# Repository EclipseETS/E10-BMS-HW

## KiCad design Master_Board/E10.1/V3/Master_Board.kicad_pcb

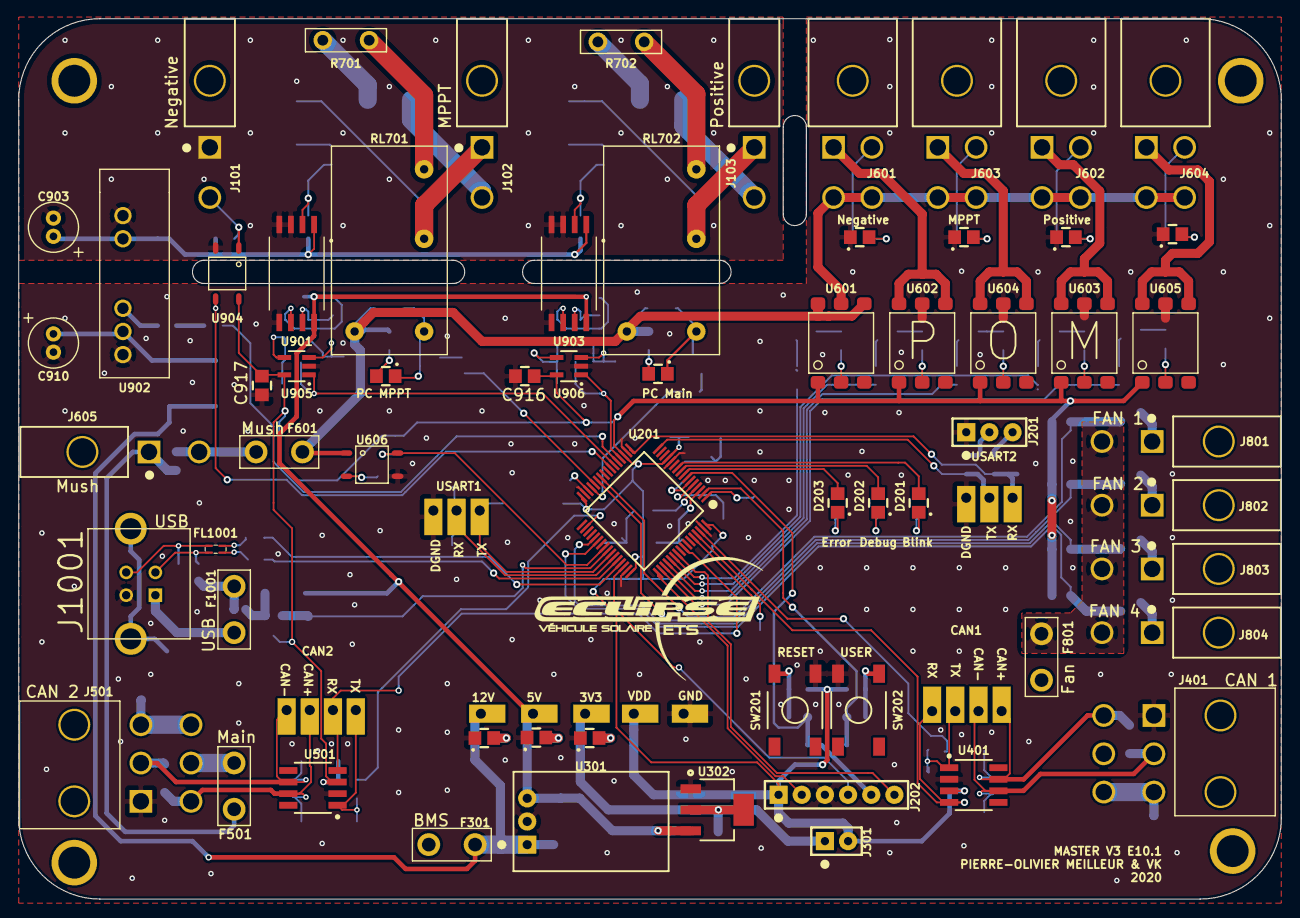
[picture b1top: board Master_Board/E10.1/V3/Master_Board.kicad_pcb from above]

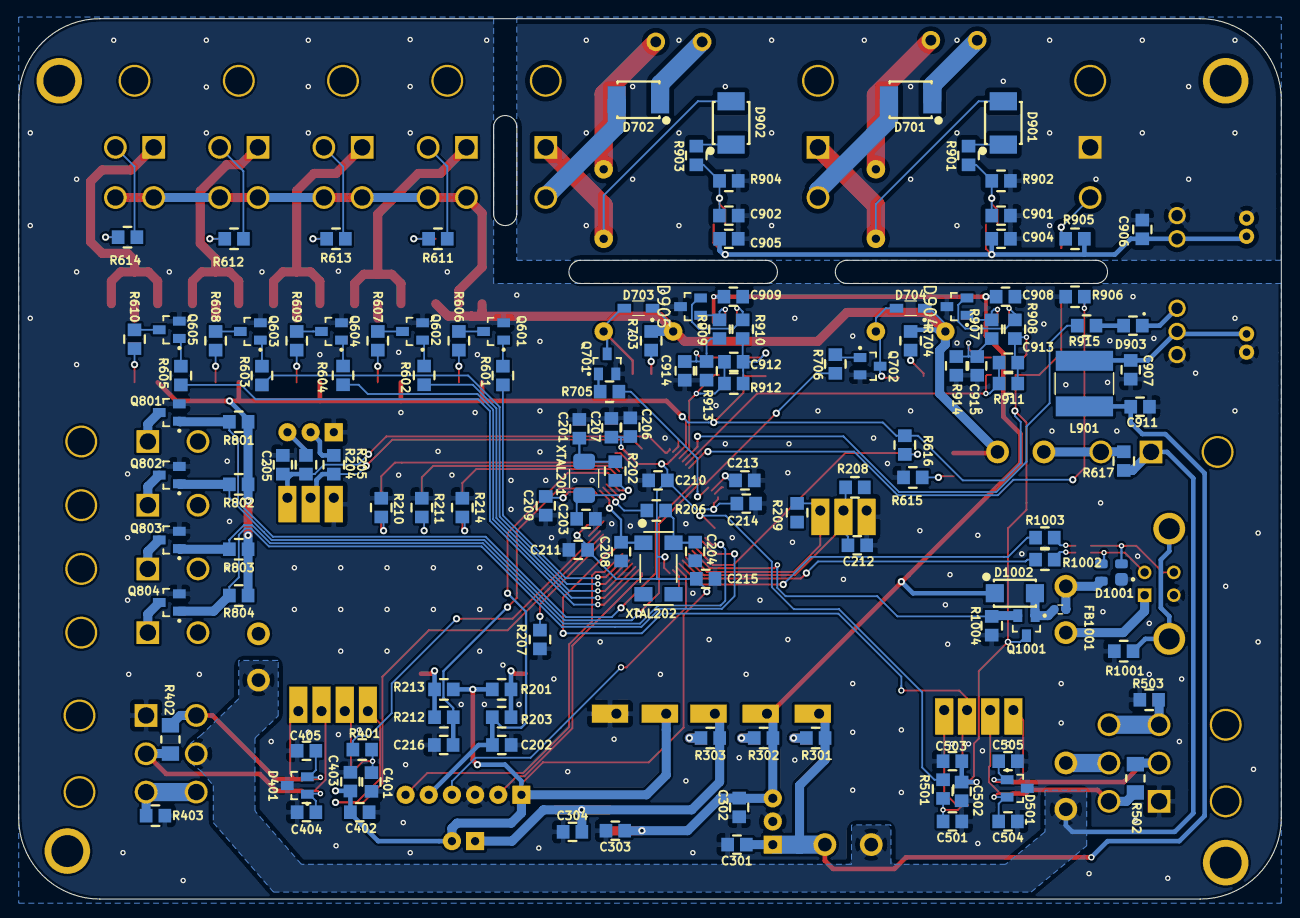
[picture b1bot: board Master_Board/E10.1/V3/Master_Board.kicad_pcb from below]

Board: 2 copper layers, 138.4 x 96.5 mm, 225 parts (139 on the bottom side), 145 nets.

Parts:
C201, C203, C205, C212, C404, C405, C504, C505: 885012007053; C0805
C202, C210, C211, C214, C215, C216, C403, C503, C904, C905, C906, C907, C908, C909, C916, C917: 885012207098; C0805
C204, C208: 885012007027; C0805
C206, C209, C402, C502: 885012107015; C0805
C207: 885012207092; C0805
C213, C301, C302: 885012107018; C0805
C303: 885012107014; C0805
C304: 885012107005; C0805
C401, C501, C901, C902, C912, C913, C914, C915: 885012207080; C0805
C903, C910: 860020472006; Radial-Can-5_11_2
C911: 885012207075; C0805
D201: 150080VS75000; LED_0805_GREEN
D202: 150080YS75000; LED_0805_YELLOW
D203: 150080RS75000; LED_0805_RED
D301, D302, D303, D601, D602, D603, D604, D705, D706: 150080BS75000; LED_0805_BLUE
D401, D501, D904, D905: D1213A-02SOL-7; SOT-23-3
D701, D702, D901, D902: NRVBS3200T3G; DO-214AA_SMB
D703, D704: NSR0530HT1G; SOD-323
D903: SD0805S020S1R0; Diode_0805
D1001: 8240026; SOT-143-4
D1002: B240AQ-13-F; DO-214AC_SMA
F301, F501, F601, F801: 39511000440; TE5_395
F1001: 39505000440; TE5_395
FB1001: 742792605; FB0603
FL1001: 744230900
H101, H102, H103, H104: Mounting-Hole-M3; Mounting_Hole_3mm
J101, J102, J103, J605, J801, J802, J803, J804: 649002227222
J201: Header_Male_Pin_2.54mm_1X3_,_Unshrouded; Headers_2.54mm_1X3
J202: Header_Male_Pin_2.54mm_1X6_,_Unshrouded; Headers_2.54mm_1X6
J301: Header_Male_Pin_2.54mm_1X2_,_Unshrouded; Headers_2.54mm_1X2
J401, J501: 649006227222
J601, J602, J603, J604: 649004227222
J1001: 61400413321
L901: 744052471; WE-TPC-SMD
Q601, Q602, Q603, Q604, Q605, Q701, Q702: BC849BLT1G; SOT-23-3
Q801, Q802, Q803, Q804, Q1001: BSS806NH6327XTSA1; SOT-23-3
R201, R204, R208, R213, R301, R905, R906, R1004: RC0805JR-074K7L; R0805
R202, R206, R403, R503, R1001, R1002, R1003: RC0805JR-070RL; R0805
R203, R212, R401, R501: RC0805JR-07100RL; R0805
R205, R209, R302, R611, R612, R613, R614, R703, R704: RC0805JR-071KL; R0805
R207, R601, R602, R603, R604, R605, R616, R705, R706, R801, R802, R803, R804, R902, R904, R907, R908, R909, R910: RC0805JR-0710KL; R0805
R210, R211, R214, R303, R915: RC0805JR-07470RL; R0805
R402, R502: RC1206JR-07120RL; R1206
R606, R607, R608, R609, R610: RC0805FR-071K1L; R0805
R615, R911, R912, R913, R914: RC0805JR-0715KL; R0805
R617: 0hms_0.5W; R0805
R701, R702: TR50JBC100R; TR50
R901, R903: RC0805JR-071ML; R0805
RL701, RL702: ALQ312
SW201, SW202: PTS645SM43SMTR92; PTS645_6X6X4_SMD
TP201, TP202, TP203, TP204, TP205, TP206, TP301, TP302, TP303, TP304, TP305, TP401, TP402, TP403, TP404, TP501, TP502, TP503, TP504: Test_Point_THM; Keystone_5001
U201: STM32F446RE; LQFP-64
U301: OKI-78SR-5_1.5-W36H-C; OKI-78SR_Horizontal
U302: AZ1117IH-3.3TRG1; SOT-223-3
U401, U501: SN65HVD232DR; SOIC-8
U601, U602, U603, U604, U605: TLP3543A(TP1,F; 6-SMD
U606, U904: CPC1117NTR; 4-SOP
U901, U903: ACPL-C87A-500E; SSO-8
U902: NCS1S2405SC
U905, U906: LMV321RILT; SOT-23-5
XTAL201: 7A-8.000MAHJ-T; TXC_7A_Series
XTAL202: ABS25-32.768KHZ-6-T; ABS25

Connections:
3.3V: C304.2, J301.1, R303.2, TP304.1, U302.2, U302.4
5V: C302.2, C303.2, C908.2, C909.2, D1002.1, R302.2, TP303.1, U301.3, U302.3, U901.8, U903.8
5V_HP: C903.1, C904.2, C905.2, C906.1, R905.1, U901.1, U902.6, U903.1
12V: C301.2, C911.1, F301.2, L901.2, R301.2, TP301.1, U301.1
/12V_Mush: D703.1, D704.1, F601.2, R703.1, R704.1, RL701.1, RL702.1, U601.4, U601.6, U606.1
/BOOT0: R207.2, U201.60
/CAN1/CAN_N: C404.1, D401.1, J401.2, R402.2, TP404.1, U401.6
/CAN1/CAN_P: C405.1, D401.2, J401.4, R402.1, TP403.1, U401.7
/CAN1/Shield1: J401.3, J401.6, R403.1
/CAN2/CAN2_H: C504.1, D501.2, J501.4, R502.1, TP503.1, U501.7
/CAN2/CAN2_L: C505.1, D501.1, J501.2, R502.2, TP504.1, U501.6
/CAN2/Shield2: J501.3, J501.6, R503.1
/Fan Control/12V_FANS: F801.2, J801.2, J802.2, J803.2, J804.2
/HV_High_Side+: D702.2, J103.2
/HV_High_Side-: D902.2, J103.1, RL702.3
/HV_Low_Side+: J101.2, R905.2, U904.1
/HV_Mppt+: D701.2, J102.2
/HV_Mppt-: D901.2, J102.1, RL701.3
/NRST: C202.1, J202.5, R203.2, U201.7
/PA4: C912.1, R912.2, U201.20, U906.1
/PA5: R915.2, U201.21
/PA6: C913.2, R911.2, U201.22, U905.1
/PA7: R906.1, U201.23, U904.3
/PA8: Q1001.2, R1004.1, U201.41
/PA11: R1002.2, U201.44
/PA12: R1003.2, U201.45
/PA15: R605.1, U201.50
/PB0: Q801.1, R801.2, U201.26
/PB1: Q802.1, R802.2, U201.27
/PB2: R706.2, U201.28
/PB5: TP502.1, U201.57, U501.4
/PB8: TP402.1, U201.61, U401.4
/PB9: R401.1, U201.62
/PB10: R705.2, U201.29
/PB13: R501.1, U201.34
/PC0: D203.2, U201.8
/PC1: D202.2, U201.9
/PC2: D201.2, U201.10
/PC6: Q803.1, R803.2, U201.37
/PC7: Q804.1, R804.2, U201.38
/PC9: R616.2, U201.40, U606.4
/PC10: R604.1, U201.51
/PC11: R602.1, U201.52
/PC12: R603.1, U201.53
/PD2: R601.1, U201.54
/STM32F446/PA2_TX: R205.2, TP201.1, U201.16
/STM32F446/PA3_RX: C205.2, R204.2, TP202.1, U201.17
/STM32F446/PA9_TX: R209.2, TP205.1, U201.42
/STM32F446/PA10_RX: C212.2, R208.2, TP204.1, U201.43
/STM32F446/SWCLK: J202.2, U201.49
/STM32F446/SWDIO: J202.4, U201.46
/STM32F446/SWO: J202.6, U201.55
/STM32F446/USART2_RX: J201.3, R204.1
/STM32F446/USART2_TX: J201.2, R205.1
/STM32F446/USER_BTN: C216.1, R212.2, U201.2
/USB/5V_EXT: D1002.2, FB1001.2, Q1001.1
/USB/D+: D1001.2, FL1001.1, J1001.3
/USB/D-: D1001.3, FL1001.4, J1001.2
/USB/Shield_Connector: J1001.5, J1001.6, R1001.1
/VBat: C209.2, U201.1
/Voltage Sense/BP-HV+: D902.1, R903.1
/Voltage Sense/MPPT-HV+: D901.1, R901.1
AGND: C901.2, C902.2, C903.2, C904.1, C905.1, C906.2, J101.1, R902.2, R904.2, U901.3, U901.4, U902.7, U903.3, U903.4, U904.2
CAN_PWR: F301.1, F501.2, F801.1, J401.5, J605.1, R617.1
DGND: C201.1, C202.2, C203.2, C204.1, C205.1, C206.1, C207.1, C208.2, C209.1, C210.2, C211.1, C212.1, C213.1, C214.2, C215.2, C216.2, C301.1, C302.1, C303.1, C304.1, C401.1, C402.1, C403.1, C404.2, C405.2, C501.2, C502.1, C503.1, C504.2, C505.2, C907.2, C908.1, C909.1, C910.2, C911.2, C914.1, C915.1, C916.2, C917.2, D301.1, D302.1, D303.1, D401.3, D501.3, D601.1, D602.1, D603.1, D604.1, D904.3, D905.3, D1001.1, J201.1, J202.3, J401.1, J501.1, J1001.4, Q601.2, Q602.2, Q603.2, Q604.2, Q605.2, Q701.2, Q702.2, Q801.2, Q802.2, Q803.2, Q804.2, R207.1, R210.1, R211.1, R214.1, R403.2, R503.2, R615.2, R906.2, R913.2, R914.2, R1001.2, R1004.2, SW201.4, SW202.3, TP203.1, TP206.1, TP302.1, U201.12, U201.18, U201.31, U201.47, U201.63, U301.2, U302.1, U401.2, U501.2, U602.5, U603.5, U604.5, U605.5, U606.3, U901.5, U902.1, U903.5, U905.2, U906.2
unnamed: C201.2, R202.2, XTAL201.1
unnamed: C203.1, U201.5, XTAL201.2
unnamed: C204.2, R206.2, XTAL202.4
unnamed: C208.1, U201.3, XTAL202.1
unnamed: C213.2, U201.30
unnamed: C401.2, R401.2, TP401.1, U401.1
unnamed: C501.1, R501.2, TP501.1, U501.1
unnamed: C901.1, R901.2, R902.1, U901.2
unnamed: C902.1, R903.2, R904.1, U903.2
unnamed: C907.1, C910.1, L901.1, U902.2
unnamed: C912.2, R910.2, R912.1, U906.4
unnamed: C913.1, R908.2, R911.1, U905.4
unnamed: C914.2, R909.2, R913.1, U906.3
unnamed: C915.2, R907.2, R914.1, U905.3
unnamed: D201.1, R210.2
unnamed: D202.1, R211.2
unnamed: D203.1, R214.2
unnamed: D301.2, R301.1
unnamed: D302.2, R302.1
unnamed: D303.2, R303.1
unnamed: D601.2, R611.2
unnamed: D602.2, R612.2
unnamed: D603.2, R613.2
unnamed: D604.2, R614.2
unnamed: D701.1, R701.1
unnamed: D702.1, R702.1
unnamed: D703.2, D705.1, Q701.3, RL702.2
unnamed: D704.2, D706.1, Q702.3, RL701.2
unnamed: D705.2, R703.2
unnamed: D706.2, R704.2
unnamed: D903.1, U902.3
unnamed: D903.2, R915.1
unnamed: D904.1, R907.1, U901.7
unnamed: D904.2, R908.1, U901.6
unnamed: D905.1, R909.1, U903.7
unnamed: D905.2, R910.1, U903.6
unnamed: D1001.4, F1001.2, FB1001.1
unnamed: F501.1, J501.5
unnamed: F601.1, J605.2, R617.2
unnamed: F1001.1, J1001.1
unnamed: FL1001.2, R1003.1
unnamed: FL1001.3, R1002.1
unnamed: J601.1, U602.4, U602.6
unnamed: J601.2, R611.1
unnamed: J601.3, J601.4, J602.3, J602.4, J603.3, J603.4, J604.3, J604.4, U601.5
unnamed: J602.1, U603.4, U603.6
unnamed: J602.2, R612.1
unnamed: J603.1, U604.4, U604.6
unnamed: J603.2, R613.1
unnamed: J604.1, U605.4, U605.6
unnamed: J604.2, R614.1
unnamed: J801.1, Q801.3
unnamed: J802.1, Q802.3
unnamed: J803.1, Q803.3
unnamed: J804.1, Q804.3
unnamed: Q601.1, R601.2
unnamed: Q601.3, R606.1
unnamed: Q602.1, R602.2
unnamed: Q602.3, R607.1
unnamed: Q603.1, R603.2
unnamed: Q603.3, R608.1
unnamed: Q604.1, R604.2
unnamed: Q604.3, R609.1
unnamed: Q605.1, R605.2
unnamed: Q605.3, R610.1
unnamed: Q701.1, R705.1
unnamed: Q702.1, R706.1
unnamed: R201.1, R203.1, SW201.2
unnamed: R202.1, U201.6
unnamed: R206.1, U201.4
unnamed: R212.1, R213.1, SW202.1
unnamed: R606.2, U601.2
unnamed: R607.2, U602.2
unnamed: R608.2, U603.2
unnamed: R609.2, U604.2
unnamed: R610.2, U605.2
unnamed: R615.1, U606.2
unnamed: R701.2, RL701.4
unnamed: R702.2, RL702.4
VDD: C206.2, C207.2, C210.1, C211.2, C214.1, C215.1, C402.2, C403.2, C502.2, C503.2, C916.1, C917.1, J202.1, J301.2, Q1001.3, R201.2, R213.2, R616.1, R801.1, R802.1, R803.1, R804.1, TP305.1, U201.13, U201.19, U201.32, U201.48, U201.64, U401.3, U501.3, U601.1, U602.1, U603.1, U604.1, U605.1, U904.4, U905.5, U906.5

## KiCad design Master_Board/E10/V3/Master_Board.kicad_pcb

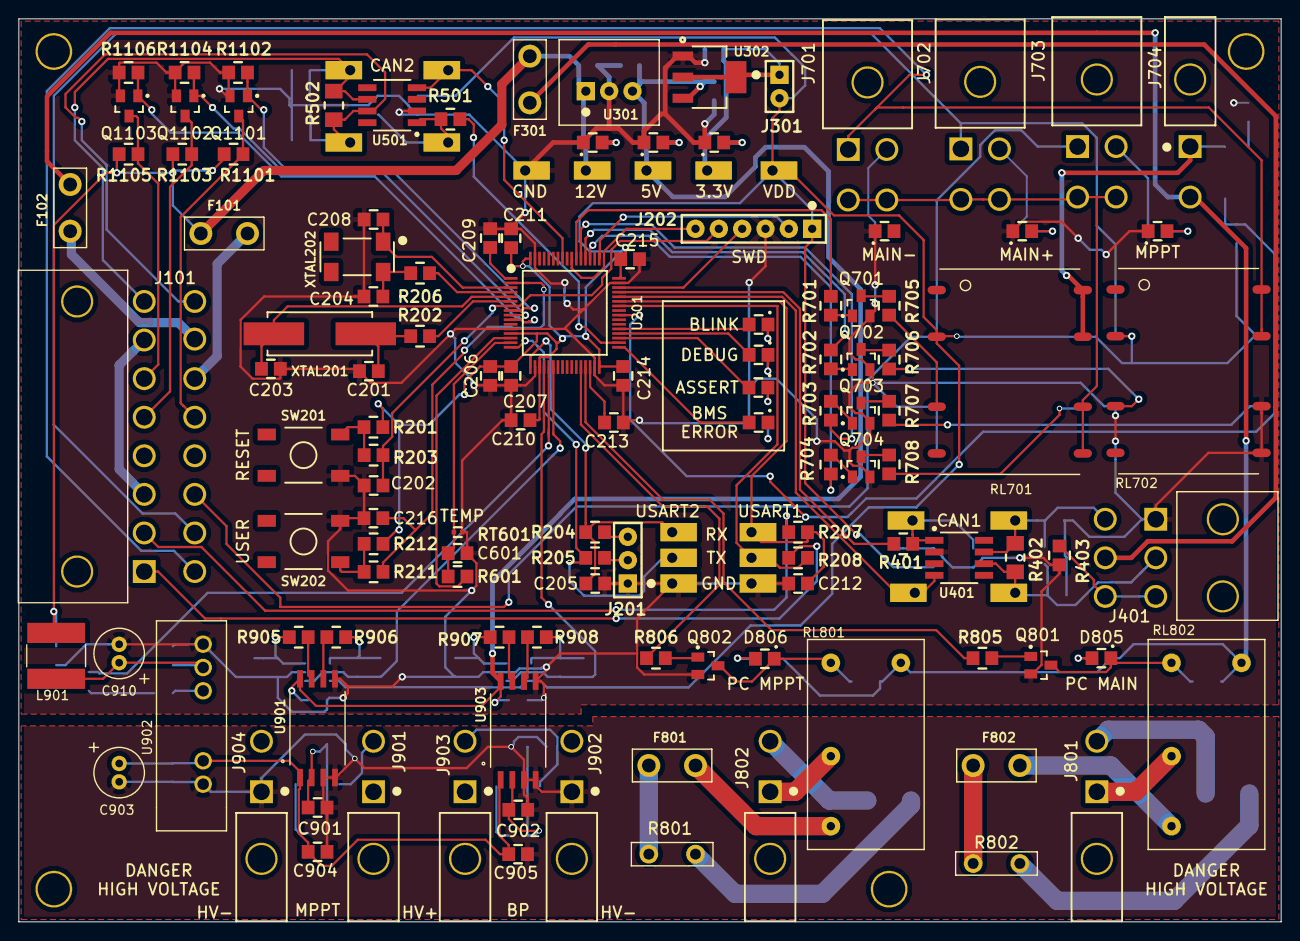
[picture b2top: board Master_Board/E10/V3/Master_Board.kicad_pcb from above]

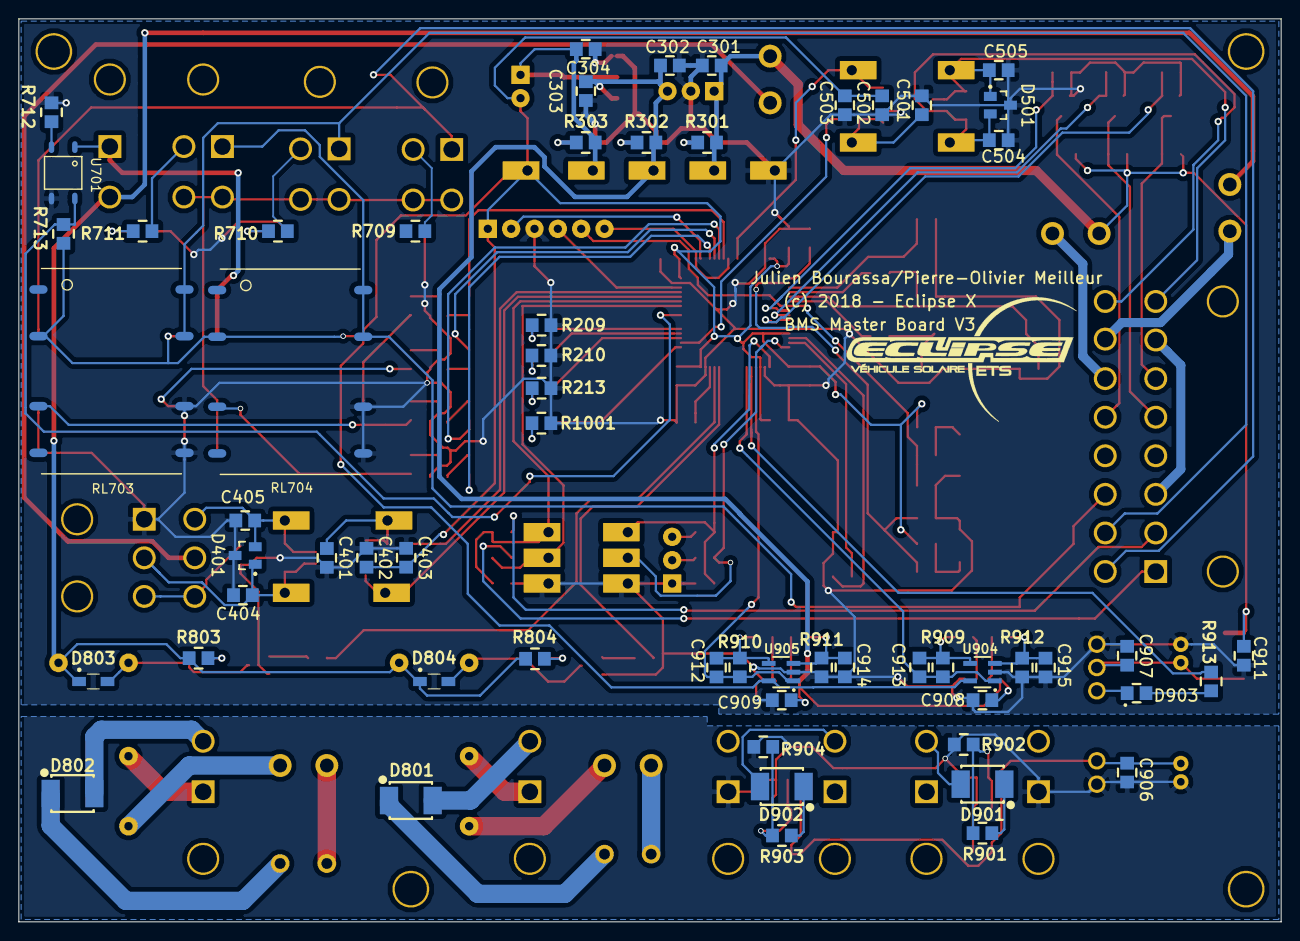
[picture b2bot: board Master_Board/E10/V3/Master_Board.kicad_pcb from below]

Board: 2 copper layers, 137.4 x 98.3 mm, 199 parts (60 on the bottom side), 132 nets.

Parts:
C201, C203, C205, C212, C404, C405, C504, C505: 885012007053; C0805
C202, C210, C211, C214, C215, C216, C403, C503, C904, C905, C906, C907, C908, C909: 885012207098; C0805
C204, C208: 885012007027; C0805
C206, C209, C402, C502, C601: 885012107015; C0805
C207: 885012207092; C0805
C213, C301, C302: 885012107018; C0805
C303: 885012107014; C0805
C304: 885012107005; C0805
C401, C501, C901, C902, C912, C913, C914, C915: 885012207080; C0805
C903, C910: 860020472006; Radial-Can-5_11_2
C911: 885012207075; C0805
D201, D301, D302, D303, D701, D702, D703, D805, D806: 150080VS75000; LED_0805_GREEN
D202: 150080YS75000; LED_0805_YELLOW
D203, D1001: 150080RS75000; LED_0805_RED
D401, D501: D1213A-02SOL-7; SOT-23-3
D801, D802, D901, D902: NRVBS3200T3G; DO-214AA_SMB
D803, D804: NSR0530HT1G; SOD-323
D903: SD0805S020S1R0; Diode_0805
F101: 39505000440; TE5_395
F102, F301: 39511000440; TE5_395
F801, F802: 80812000440; TE5_395
J101: 649016227222
J201: Header_Male_Pin_2.54mm_1X3_,_Unshrouded; Headers_2.54mm_1X3
J202: Header_Male_Pin_2.54mm_1X6_,_Unshrouded; Headers_2.54mm_1X6
J301: Header_Male_Pin_2.54mm_1X2_,_Unshrouded; Headers_2.54mm_1X2
J401: 649006227222
J701, J702, J703: 649004227222
J704, J801, J802, J901, J902, J903, J904: 649002227222
L901: 744052471; WE-TPC-SMD
Q701, Q702, Q703, Q704, Q801, Q802: BC849BLT1G; SOT-23-3
Q1101, Q1102, Q1103: BSS806NH6327XTSA1; SOT-23-3
R201, R204, R207, R212, R301, R1101, R1103, R1105: RC0805JR-074K7L; R0805
R202, R206, R403: RC0805JR-070RL; R0805
R203, R211, R401, R501: RC0805JR-07100RL; R0805
R205, R208, R302, R709, R710, R711, R803, R804: RC0805JR-071KL; R0805
R209, R210, R213, R303, R913: RC0805JR-07470RL; R0805
R402, R502: RC1206JR-07120RL; R1206
R601: RC0805JR-0733KL; R0805
R701, R702, R703, R704, R713, R805, R806, R902, R904, R905, R906, R907, R908: RC0805JR-0710KL; R0805
R705, R706, R707, R708: RC0805FR-071K1L; R0805
R712, R909, R910, R911, R912: RC0805JR-0715KL; R0805
R801, R802: TR50JBC100R; TR50
R901, R903: RC0805JR-071ML; R0805
R1001: RC0805JR-07330RL; R0805
R1102, R1104, R1106: RC0805JR-07100KL; R0805
RL701, RL702, RL703, RL704: CPC1907B
RL801, RL802: ALQ312
RT601: NCP15WB473F03RC; R0402
SW201, SW202: PTS645SM43SMTR92; PTS645_6X6X4_SMD
TP201, TP202, TP203, TP204, TP205, TP206, TP301, TP302, TP303, TP304, TP305, TP401, TP402, TP403, TP404, TP501, TP502, TP503, TP504: Test_Point_THM; Keystone_5001
U201: STM32F446RE; LQFP-64
U301: OKI-78SR-5/1.5-W36-C; OKI-78SR_Vertical
U302: AZ1117IH-3.3TRG1; SOT-223-3
U401, U501: SN65HVD232DR; SOIC-8
U701: CPC1117NTR; 4-SOP
U901, U903: ACPL-C87A-500E; SSO-8
U902: NCS1S2405SC
U904, U905: LMV321RILT; SOT-23-5
XTAL201: ABLS-8.000MHZ-D-T; HC49_US
XTAL202: ABS25-32.768KHZ-6-T; ABS25

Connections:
3.3V: C304.2, J301.1, R303.2, TP304.1, U302.2, U302.4
5V: C302.2, C303.2, C908.2, C909.2, R302.2, TP303.1, U301.3, U302.3, U901.8, U903.8
12V: C301.2, C911.1, F101.2, F301.2, L901.2, R301.2, R1101.1, R1103.1, R1105.1, TP301.1, U301.1
/12V_IN1: F101.1, J101.14
/12V_IN2: F102.1, J101.15
/CAN1/CAN_N: C404.1, D401.1, J401.2, R402.2, TP404.1, U401.6
/CAN1/CAN_P: C405.1, D401.2, J401.4, R402.1, TP403.1, U401.7
/CAN1/Shield1: J401.3, J401.6, R403.1
/CAN2_H: C504.1, D501.2, J101.16, R502.1, TP503.1, U501.7
/CAN2_L: C505.1, D501.1, J101.8, R502.2, TP504.1, U501.6
/ContactorControl/12V_Protected: J704.1, RL701.7, RL701.8, U701.1
/Contactor_12V: D803.1, D804.1, F102.2, J704.2, R803.1, R804.1, RL801.1, RL802.1
/GND: J101.3, J101.7
/IO1: J101.10, J702.1, RL703.7, RL703.8
/IO2: J101.9, J701.1, RL702.7, RL702.8
/IO3: J101.11, J703.1, RL704.7, RL704.8
/IO5: J101.13, Q1101.3, R1101.2
/IO7: J101.5, Q1102.3, R1103.2
/IO8: J101.6, Q1103.3, R1105.2
/NRST: C202.1, J202.5, R203.2, U201.7
/NTC_1_ADC: C601.1, R601.1, RT601.2, U201.15
/NTC_1_GPIO: R601.2, U201.14
/PA4: C912.1, R910.2, U201.20, U905.1
/PA5: R913.2, U201.21
/PA6: C913.2, R909.2, U201.22, U904.1
/PA11: TP402.1, U201.44, U401.4
/PA12: R401.1, U201.45
/PB2: R806.2, U201.28
/PB5: TP502.1, U201.57, U501.4
/PB10: R805.2, U201.29
/PB12: D1001.2, U201.33
/PB13: R501.1, U201.34
/PB14: D203.2, U201.35
/PB15: D202.2, U201.36
/PC0: Q1101.1, R1102.2, U201.8
/PC1: Q1102.1, R1104.2, U201.9
/PC2: Q1103.1, R1106.2, U201.10
/PC6: D201.2, U201.37
/PC9: R713.2, U201.40, U701.4
/PC10: R704.1, U201.51
/PC11: R702.1, U201.52
/PC12: R703.1, U201.53
/PD2: R701.1, U201.54
/RS232_RX: J101.2, R207.1
/RS232_TX: J101.1, R208.1
/STM32F446/PA2_TX: R205.2, TP201.1, U201.16
/STM32F446/PA3_RX: C205.2, R204.2, TP202.1, U201.17
/STM32F446/PA9_TX: R208.2, TP205.1, U201.42
/STM32F446/PA10_RX: C212.2, R207.2, TP204.1, U201.43
/STM32F446/SWCLK: J202.2, U201.49
/STM32F446/SWDIO: J202.4, U201.46
/STM32F446/SWO: J202.6, U201.55
/STM32F446/USART2_RX: J201.3, R204.1
/STM32F446/USART2_TX: J201.2, R205.1
/STM32F446/USER_BTN: C216.1, R211.2, U201.2
/VBat: C209.2, U201.1
/Voltage Sense/5V_ISO: C903.1, C904.2, C905.2, C906.1, U901.1, U902.6, U903.1
/Voltage Sense/BP-HV+: D902.1, R903.1
/Voltage Sense/MPPT-HV+: D901.1, R901.1
AGND: C901.2, C902.2, C903.2, C904.1, C905.1, C906.2, J902.1, J904.1, R902.2, R904.2, U901.3, U901.4, U902.7, U903.3, U903.4
CAN_PWR: F301.1, J401.5
DGND: C201.1, C202.2, C203.2, C204.1, C205.1, C206.1, C207.1, C208.2, C209.1, C210.2, C211.1, C212.1, C213.1, C214.2, C215.2, C216.2, C301.1, C302.1, C303.1, C304.1, C401.1, C402.1, C403.1, C404.2, C405.2, C501.2, C502.1, C503.1, C504.2, C505.2, C601.2, C907.2, C908.1, C909.1, C910.2, C911.2, C914.1, C915.1, D301.1, D302.1, D303.1, D401.3, D501.3, D701.1, D702.1, D703.1, J201.1, J202.3, J401.1, Q701.2, Q702.2, Q703.2, Q704.2, Q801.2, Q802.2, Q1101.2, Q1102.2, Q1103.2, R209.1, R210.1, R213.1, R403.2, R712.2, R911.2, R912.2, R1001.1, R1102.1, R1104.1, R1106.1, RL702.5, RL702.6, RL703.5, RL703.6, RL704.5, RL704.6, RT601.1, SW201.4, SW202.3, TP203.1, TP206.1, TP302.1, U201.12, U201.18, U201.31, U201.47, U201.63, U301.2, U302.1, U401.2, U501.2, U701.3, U901.5, U902.1, U903.5, U904.2, U905.2
unnamed: C201.2, R202.2, XTAL201.1
unnamed: C203.1, U201.5, XTAL201.2
unnamed: C204.2, R206.2, XTAL202.4
unnamed: C208.1, U201.3, XTAL202.1
unnamed: C213.2, U201.30
unnamed: C401.2, R401.2, TP401.1, U401.1
unnamed: C501.1, R501.2, TP501.1, U501.1
unnamed: C901.1, R901.2, R902.1, U901.2
unnamed: C902.1, R903.2, R904.1, U903.2
unnamed: C907.1, C910.1, L901.1, U902.2
unnamed: C912.2, R908.2, R910.1, U905.4
unnamed: C913.1, R906.2, R909.1, U904.4
unnamed: C914.2, R907.2, R911.1, U905.3
unnamed: C915.2, R905.2, R912.1, U904.3
unnamed: D201.1, R209.2
unnamed: D202.1, R210.2
unnamed: D203.1, R213.2
unnamed: D301.2, R301.1
unnamed: D302.2, R302.1
unnamed: D303.2, R303.1
unnamed: D701.2, R709.2
unnamed: D702.2, R710.2
unnamed: D703.2, R711.2
unnamed: D801.1, R801.1
unnamed: D801.2, J802.2
unnamed: D802.1, R802.1
unnamed: D802.2, J801.2
unnamed: D803.2, D805.1, Q801.3, RL802.2
unnamed: D804.2, D806.1, Q802.3, RL801.2
unnamed: D805.2, R803.2
unnamed: D806.2, R804.2
unnamed: D901.2, J901.2
unnamed: D902.2, J903.2
unnamed: D903.1, U902.3
unnamed: D903.2, R913.1
unnamed: D1001.1, R1001.2
unnamed: F801.1, R801.2
unnamed: F801.2, RL801.4
unnamed: F802.1, R802.2
unnamed: F802.2, RL802.4
unnamed: J701.2, R709.1
unnamed: J701.3, J701.4, J702.3, J702.4, J703.3, J703.4, RL701.5, RL701.6
unnamed: J702.2, R710.1
unnamed: J703.2, R711.1
unnamed: J801.1, RL802.3
unnamed: J802.1, RL801.3
unnamed: Q701.1, R701.2
unnamed: Q701.3, R705.1
unnamed: Q702.1, R702.2
unnamed: Q702.3, R706.1
unnamed: Q703.1, R703.2
unnamed: Q703.3, R707.1
unnamed: Q704.1, R704.2
unnamed: Q704.3, R708.1
unnamed: Q801.1, R805.1
unnamed: Q802.1, R806.1
unnamed: R201.1, R203.1, SW201.2
unnamed: R202.1, U201.6
unnamed: R206.1, U201.4
unnamed: R211.1, R212.1, SW202.1
unnamed: R705.2, RL701.3
unnamed: R706.2, RL702.3
unnamed: R707.2, RL703.3
unnamed: R708.2, RL704.3
unnamed: R712.1, U701.2
unnamed: R905.1, U901.7
unnamed: R906.1, U901.6
unnamed: R907.1, U903.7
unnamed: R908.1, U903.6
VDD: C206.2, C207.2, C210.1, C211.2, C214.1, C215.1, C402.2, C403.2, C502.2, C503.2, J202.1, J301.2, R201.2, R212.2, R713.1, RL701.2, RL702.2, RL703.2, RL704.2, TP305.1, U201.13, U201.19, U201.32, U201.48, U201.64, U401.3, U501.3, U904.5, U905.5

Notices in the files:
Current_Sense/V1/Isolated_BMS_Slave_Current_Sense.kicad_pcb:
(c) 2017 - Eclipse X
Master_Board/E10/V3/Master_Board.kicad_pcb:
(c) 2018 - Eclipse X
